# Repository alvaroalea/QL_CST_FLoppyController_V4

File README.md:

# QL_CST_FLoppyController

A clone of some version of the CST's Floppy Disk Interface for Sinclair QL

## History

CST was one of the main manufacturer of add-on for the Sinclair QL computer, this include backplanes, memory expansions and disc interfaces.

The Disk interface evolved over several version, with enhaced compatibilities in each version.

- Issue 1 - I can't get information about this Issue on internet.
- Issue 2 - This version use ReVision 1.13 (C) 1985 of the ROM, of 8Kb, Nicolaos Doukas draw the schematic an create a clone. Is possible to upgrade Issue 2 to ROM 1.16 if isolate the PIN 3 of IC3 (74LS03).
- Issue 3 - This version use Revision 1.16 (C) 198X of the ROM, of 8Kb, new clock circuit and 1 missing track on the PCB (and this is the reason you need to isolate pin 3 on Issue 2)
- Issue 4 - This version use Revision 1.18 (C) 1986 /1.19 (C) 1987 of the ROM, diferent circuit, increase the ROM size to 12Kb (use a 16Kb Eprom chip), now include RAM disk driver in rom, this version se a scrambled ROM, so when read with a external device, you can see the code.

Version 1.19 of ROM is missing in action, other version area available to download here: https://dilwyn.theqlforum.com/qlrom/index.html

Has been seen version of Issue 4 with, the top/botton cooper tracks interchanged, this help to reverse engineered the complete board.

Nowday I have draw and test the PCB of Issue 3 and 4, they are in separate folders, including, manuals and and ROM image.

## The Board

It use the standar stugart conector, so a plain cable can have up to 2 disk drives, that shall be correctly configured as DS0 and DS1.

It use a WD1770 disc controller, and is expected that will be compatible with WD1772 (not checked), WD1773 is not compatible.

Thanks to Derek_Stewart and techy of qlforum.co.uk for providing the pictures that allow me to capture the schema.

A interactive bill of materials for each board is available here:

* https://alvaroalea.github.io/QL_CST_FLoppyController/ibom_3.html
* https://alvaroalea.github.io/QL_CST_FLoppyController/ibom_4.html

### WARNING: Use good components!

During testing we found that bulk unknow 2N2222 transistor seen to work, but have hard compatibility problems with other boards.

Using a wellknow source transistor eliminate the incompatibility and work correctly with other passthrough boards. Be aware if you use a external or internal RAM expansion, a Qbide with passtrough or a backplane that allow several boarda.

## Recreated Boards

### Issue 4

### Issue 3

## Original Boards

### Issue 2

One of the few images available on internet, noted the transistor near the edge conector, 3 resistor on top of the PCB, two of this near the crystal, and the resistor array near WD1770 is called R4 (SIL)

### Issue 3

The transistor has been moved, the 3 resistor has been replaces by array R1, and the resistor array near WD1770 is called R2 (SIL)

### Issue 4

Complete new PCB, note The right one, with top/botton layer correct, but without silkscreen, and the left, with silkscreen but top/botton swapped (and exposed tracks under heat disipator).

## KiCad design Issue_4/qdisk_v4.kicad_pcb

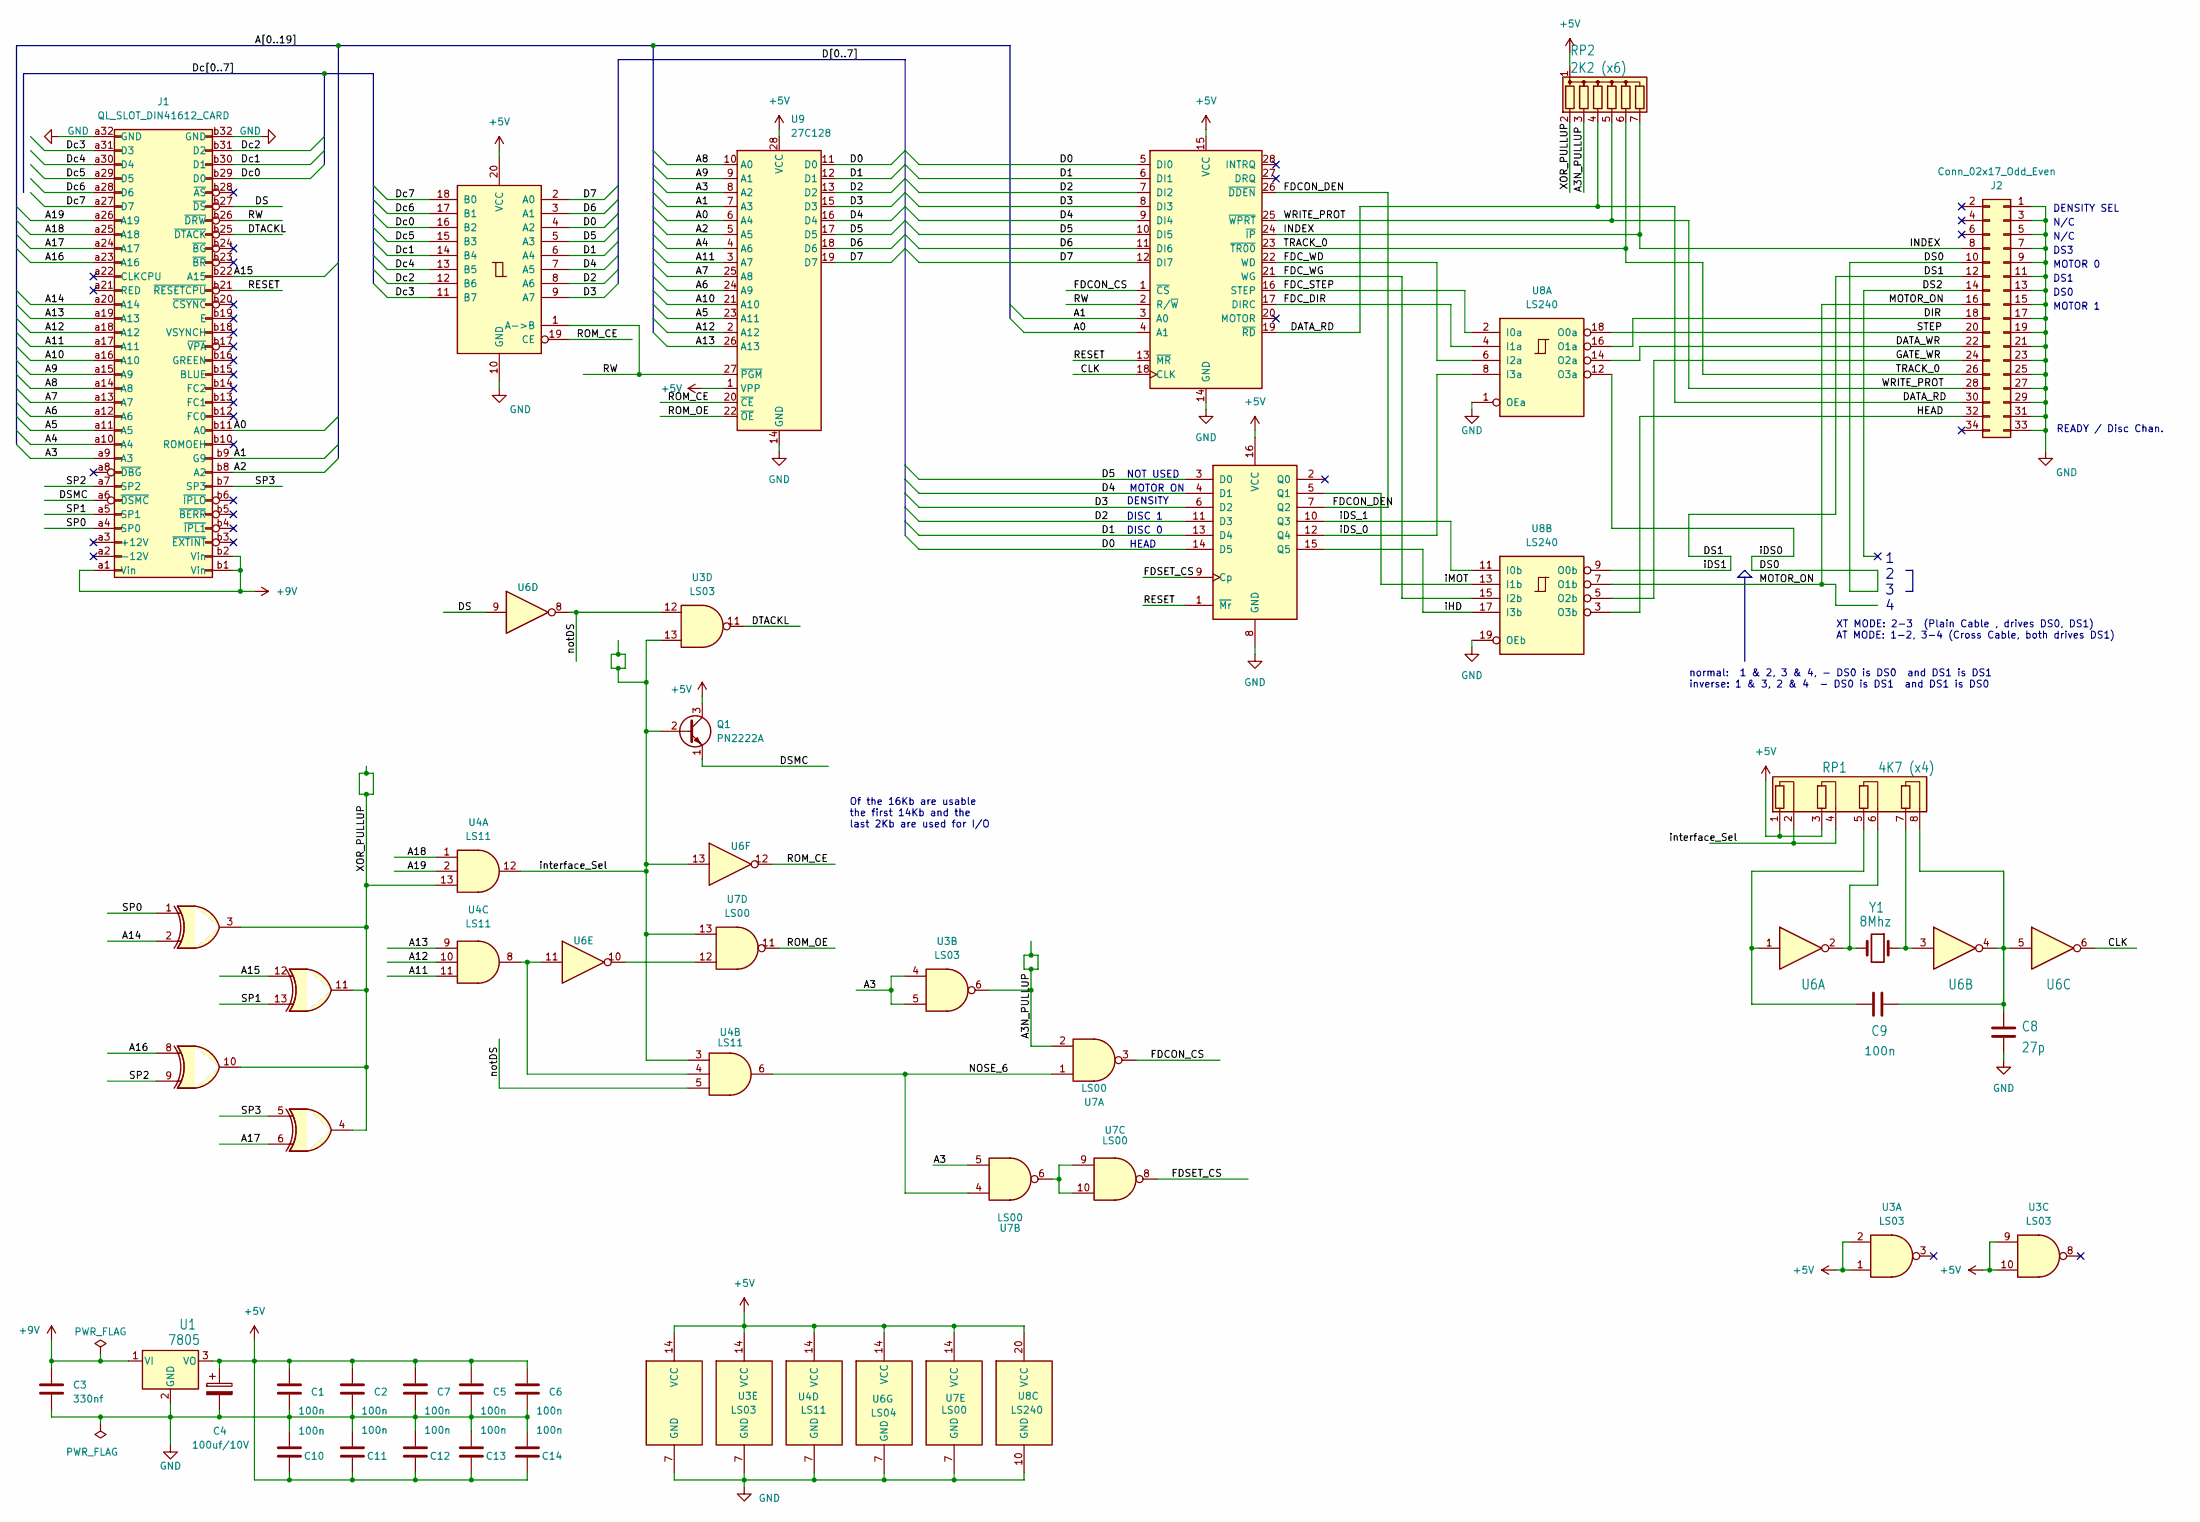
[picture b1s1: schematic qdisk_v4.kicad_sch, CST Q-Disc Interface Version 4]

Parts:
C1, C2, C5, C6, C7, C9, C10, C11, C12, C13, C14: 100n; C_Disc_D7.0mm_W2.5mm_P5.00mm
C3: 330nf; C_Disc_D7.0mm_W2.5mm_P5.00mm
C4: 100uf/10V; CP_Radial_D8.0mm_P5.00mm
C8: 27p; C_Disc_D7.0mm_W2.5mm_P5.00mm
J1: QL_SLOT_DIN41612_CARD; DIN41612_B_2x32_Female_Horizontal_THT
J2: Conn_02x17_Odd_Even; IDC-Header_2x17_P2.54mm_Latch_Horizontal
Q1: PN2222A; TO-92S_Wide
RP1: 4K7 (x4); R_Array_SIP8
RP2: 2K2 (x6); R_Array_SIP7
U1: 7805; TO-220-3_Horizontal_TabDown
U2: 74LS266; DIP-14_W7.62mm
U3: LS03; DIP-14_W7.62mm_Socket
U4: LS11; DIP-14_W7.62mm_Socket
U5: 74LS245; DIP-20_W7.62mm_Socket
U6: LS04; DIP-14_W7.62mm_Socket
U7: LS00; DIP-14_W7.62mm_Socket
U8: LS240; DIP-20_W7.62mm_Socket
U9: 27C128; DIP-28_W15.24mm_Socket
U10: FDC_WD1772; DIP-28_W15.24mm
U11: 74LS174; DIP-16_W7.62mm_Socket
Y1: 8Mhz; Crystal_HC18-U_Horizontal

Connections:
+5V: C1.1, C2.1, C4.1, C5.1, C6.1, C7.1, C10.1, C11.1, C12.1, C13.1, C14.1, Q1.3 (C), RP1.1 (R1.1), RP1.3 (R2.1), RP2.1 (common), U1.3 (VO), U2.14 (VCC), U3.1, U3.2, U3.9, U3.10, U3.14 (VCC), U4.14 (VCC), U5.20 (VCC), U6.14 (VCC), U7.14 (VCC), U8.20 (VCC), U9.1 (VPP), U9.28 (VCC), U10.15 (VCC), U11.16 (VCC)
+9V: C3.1, J1.a1 (Vin), J1.b1 (Vin), J1.b2 (Vin), U1.1 (VI)
/A0: J1.b11 (A0), U9.6 (A4), U10.4 (A1)
/A1: J1.b9 (G9), U9.7 (A3), U10.3 (A0)
/A2: J1.b8 (A2), U9.5 (A5)
/A3: J1.a9 (A3), U3.4, U3.5, U7.5, U9.8 (A2)
/A3N_PULLUP: RP2.3 (R2), U3.6, U7.2
/A4: J1.a10 (A4), U9.4 (A6)
/A5: J1.a11 (A5), U9.23 (A11)
/A6: J1.a12 (A6), U9.24 (A9)
/A7: J1.a13 (A7), U9.25 (A8)
/A8: J1.a14 (A8), U9.10 (A0)
/A9: J1.a15 (A9), U9.9 (A1)
/A10: J1.a16 (A10), U9.21 (A10)
/A11: J1.a17 (A11), U4.11, U9.3 (A7)
/A12: J1.a18 (A12), U4.10, U9.2 (A12)
/A13: J1.a19 (A13), U4.9, U9.26 (A13)
/A14: J1.a20 (A14), U2.2
/A15: J1.b22 (A15), U2.12
/A16: J1.a23 (A16), U2.8
/A17: J1.a24 (A17), U2.6
/A18: J1.a25 (A18), U4.1
/A19: J1.a26 (A19), U4.2
/CLK: U6.6, U10.18 (CLK)
/D0: U5.4 (A2), U9.11 (D0), U10.5 (DI0), U11.14 (D5)
/D1: U5.6 (A4), U9.12 (D1), U10.6 (DI1), U11.13 (D4)
/D2: U5.8 (A6), U9.13 (D2), U10.7 (DI2), U11.11 (D3)
/D3: U5.9 (A7), U9.15 (D3), U10.8 (DI3), U11.6 (D2)
/D4: U5.7 (A5), U9.16 (D4), U10.9 (DI4), U11.4 (D1)
/D5: U5.5 (A3), U9.17 (D5), U10.10 (DI5), U11.3 (D0)
/D6: U5.3 (A1), U9.18 (D6), U10.11 (DI6)
/D7: U5.2 (A0), U9.19 (D7), U10.12 (DI7)
/DATA_RD: J2.30, RP2.4 (R3), U10.19 (~RD)
/DATA_WR: J2.22, U8.14 (O2a)
/DIR: J2.18, U8.16 (O1a)
/DS: J1.b27 (~DS), U6.9
/DS0: J2.10, U8.12 (O3a)
/DS1: J2.12, U8.9 (O0b)
/DS2: J2.14
/DSMC: J1.a6 (~DSMC), Q1.1 (E)
/DTACKL: J1.b25 (~DTACK), U3.11
/Dc0: J1.b29 (D0), U5.16 (B2)
/Dc1: J1.b30 (D1), U5.14 (B4)
/Dc2: J1.b31 (D2), U5.12 (B6)
/Dc3: J1.a31 (D3), U5.11 (B7)
/Dc4: J1.a30 (D4), U5.13 (B5)
/Dc5: J1.a29 (D5), U5.15 (B3)
/Dc6: J1.a28 (D6), U5.17 (B1)
/Dc7: J1.a27 (D7), U5.18 (B0)
/FDCON_CS: U7.3, U10.1 (~CS)
/FDCON_DEN: U10.26 (~DDEN), U11.7 (Q2)
/FDC_DIR: U8.4 (I1a), U10.17 (DIRC)
/FDC_STEP: U8.2 (I0a), U10.16 (STEP)
/FDC_WD: U8.6 (I2a), U10.22 (WD)
/FDC_WG: U8.15 (I2b), U10.21 (WG)
/FDSET_CS: U7.8, U11.9 (Cp)
/GATE_WR: J2.24, U8.5 (O2b)
/HEAD: J2.32, U8.3 (O3b)
/INDEX: J2.8, RP2.7 (R6), U10.24 (~IP)
/MOTOR_ON: J2.16, U8.7 (O1b)
/NOSE_6: U4.6, U7.1, U7.4
/RESET: J1.b21 (~RESETCPU), U10.13 (~MR), U11.1 (~Mr)
/ROM_CE: U5.19 (CE), U6.12, U9.20 (~CE)
/ROM_OE: U7.11, U9.22 (~OE)
/RW: J1.b26 (~DRW), U5.1 (A->B), U9.27 (~PGM), U10.2 (R/~W)
/SP0: J1.a4 (SP0), U2.1
/SP1: J1.a5 (SP1), U2.13
/SP2: J1.a7 (SP2), U2.9
/SP3: J1.b7 (SP3), U2.5
/STEP: J2.20, U8.18 (O0a)
/TRACK_0: J2.26, RP2.6 (R5), U10.23 (~TR00)
/WRITE_PROT: J2.28, RP2.5 (R4), U10.25 (~WPRT)
/XOR_PULLUP: RP2.2 (R1), U2.3, U2.4, U2.10, U2.11, U4.13
/iDS_0: U8.8 (I3a), U11.12 (Q4)
/iDS_1: U8.11 (I0b), U11.10 (Q3)
/iHD: U8.17 (I3b), U11.15 (Q5)
/iMOT: U8.13 (I1b), U11.5 (Q1)
/interface_Sel: Q1.2 (B), RP1.2 (R1.2), RP1.4 (R2.2), U3.13, U4.3, U4.12, U6.13, U7.13
/notDS: U3.12, U4.5, U6.8
GND: C1.2, C2.2, C3.2, C4.2, C5.2, C6.2, C7.2, C8.2, C10.2, C11.2, C12.2, C13.2, C14.2, J1.a32 (GND), J1.b32 (GND), J2.1, J2.3, J2.5, J2.7, J2.9, J2.11, J2.13, J2.15, J2.17, J2.19, J2.21, J2.23, J2.25, J2.27, J2.29, J2.31, J2.33, U1.2 (GND), U2.7 (GND), U3.7 (GND), U4.7 (GND), U5.10 (GND), U6.7 (GND), U7.7 (GND), U8.1 (OEa), U8.10 (GND), U8.19 (OEb), U9.14 (GND), U10.14 (GND), U11.8 (GND)
unnamed: C9.2, RP1.5 (R3.1), U6.1
unnamed: RP1.6 (R3.2), U6.2, Y1.2
unnamed: RP1.7 (R4.1), U6.3, Y1.1
unnamed: C8.1, C9.1, RP1.8 (R4.2), U6.4, U6.5
unnamed: U4.4, U4.8, U6.11
unnamed: U6.10, U7.12
unnamed: U7.6, U7.9, U7.10

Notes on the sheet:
XT MODE: 2-3 (Plain Cable , drives DS0, DS1) AT MODE: 1-2, 3-4 (Cross Cable, both drives DS1)
NOT USED
MOTOR ON
MOTOR 0
HEAD
normal: 1 & 2, 3 & 4, - DS0 is DS0 and DS1 is DS1 inverse: 1 & 3, 2 & 4 - DS0 is DS1 and DS1 is DS0
DS0
DS1
READY / Disc Chan.
DENSITY
MOTOR 1
DS3
Of the 16Kb are usable the first 14Kb and the last 2Kb are used for I/O
N/C
1 2 3 4
DISC 1
DENSITY SEL
DISC 0

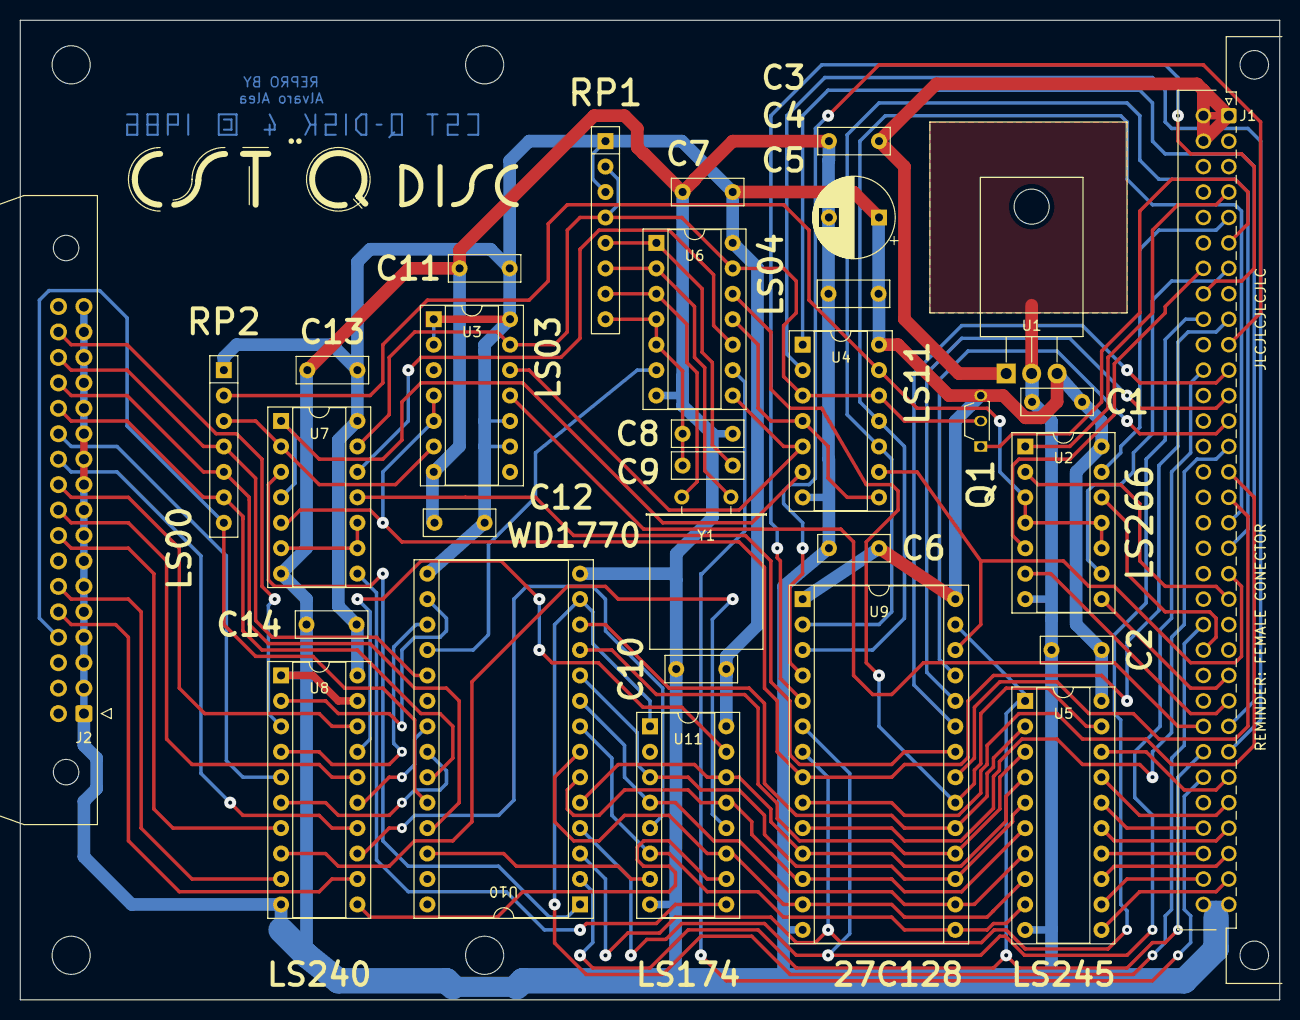
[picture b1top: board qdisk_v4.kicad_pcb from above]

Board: 2 copper layers, 125.7 x 97.8 mm, 31 parts (0 on the bottom side), 86 nets.

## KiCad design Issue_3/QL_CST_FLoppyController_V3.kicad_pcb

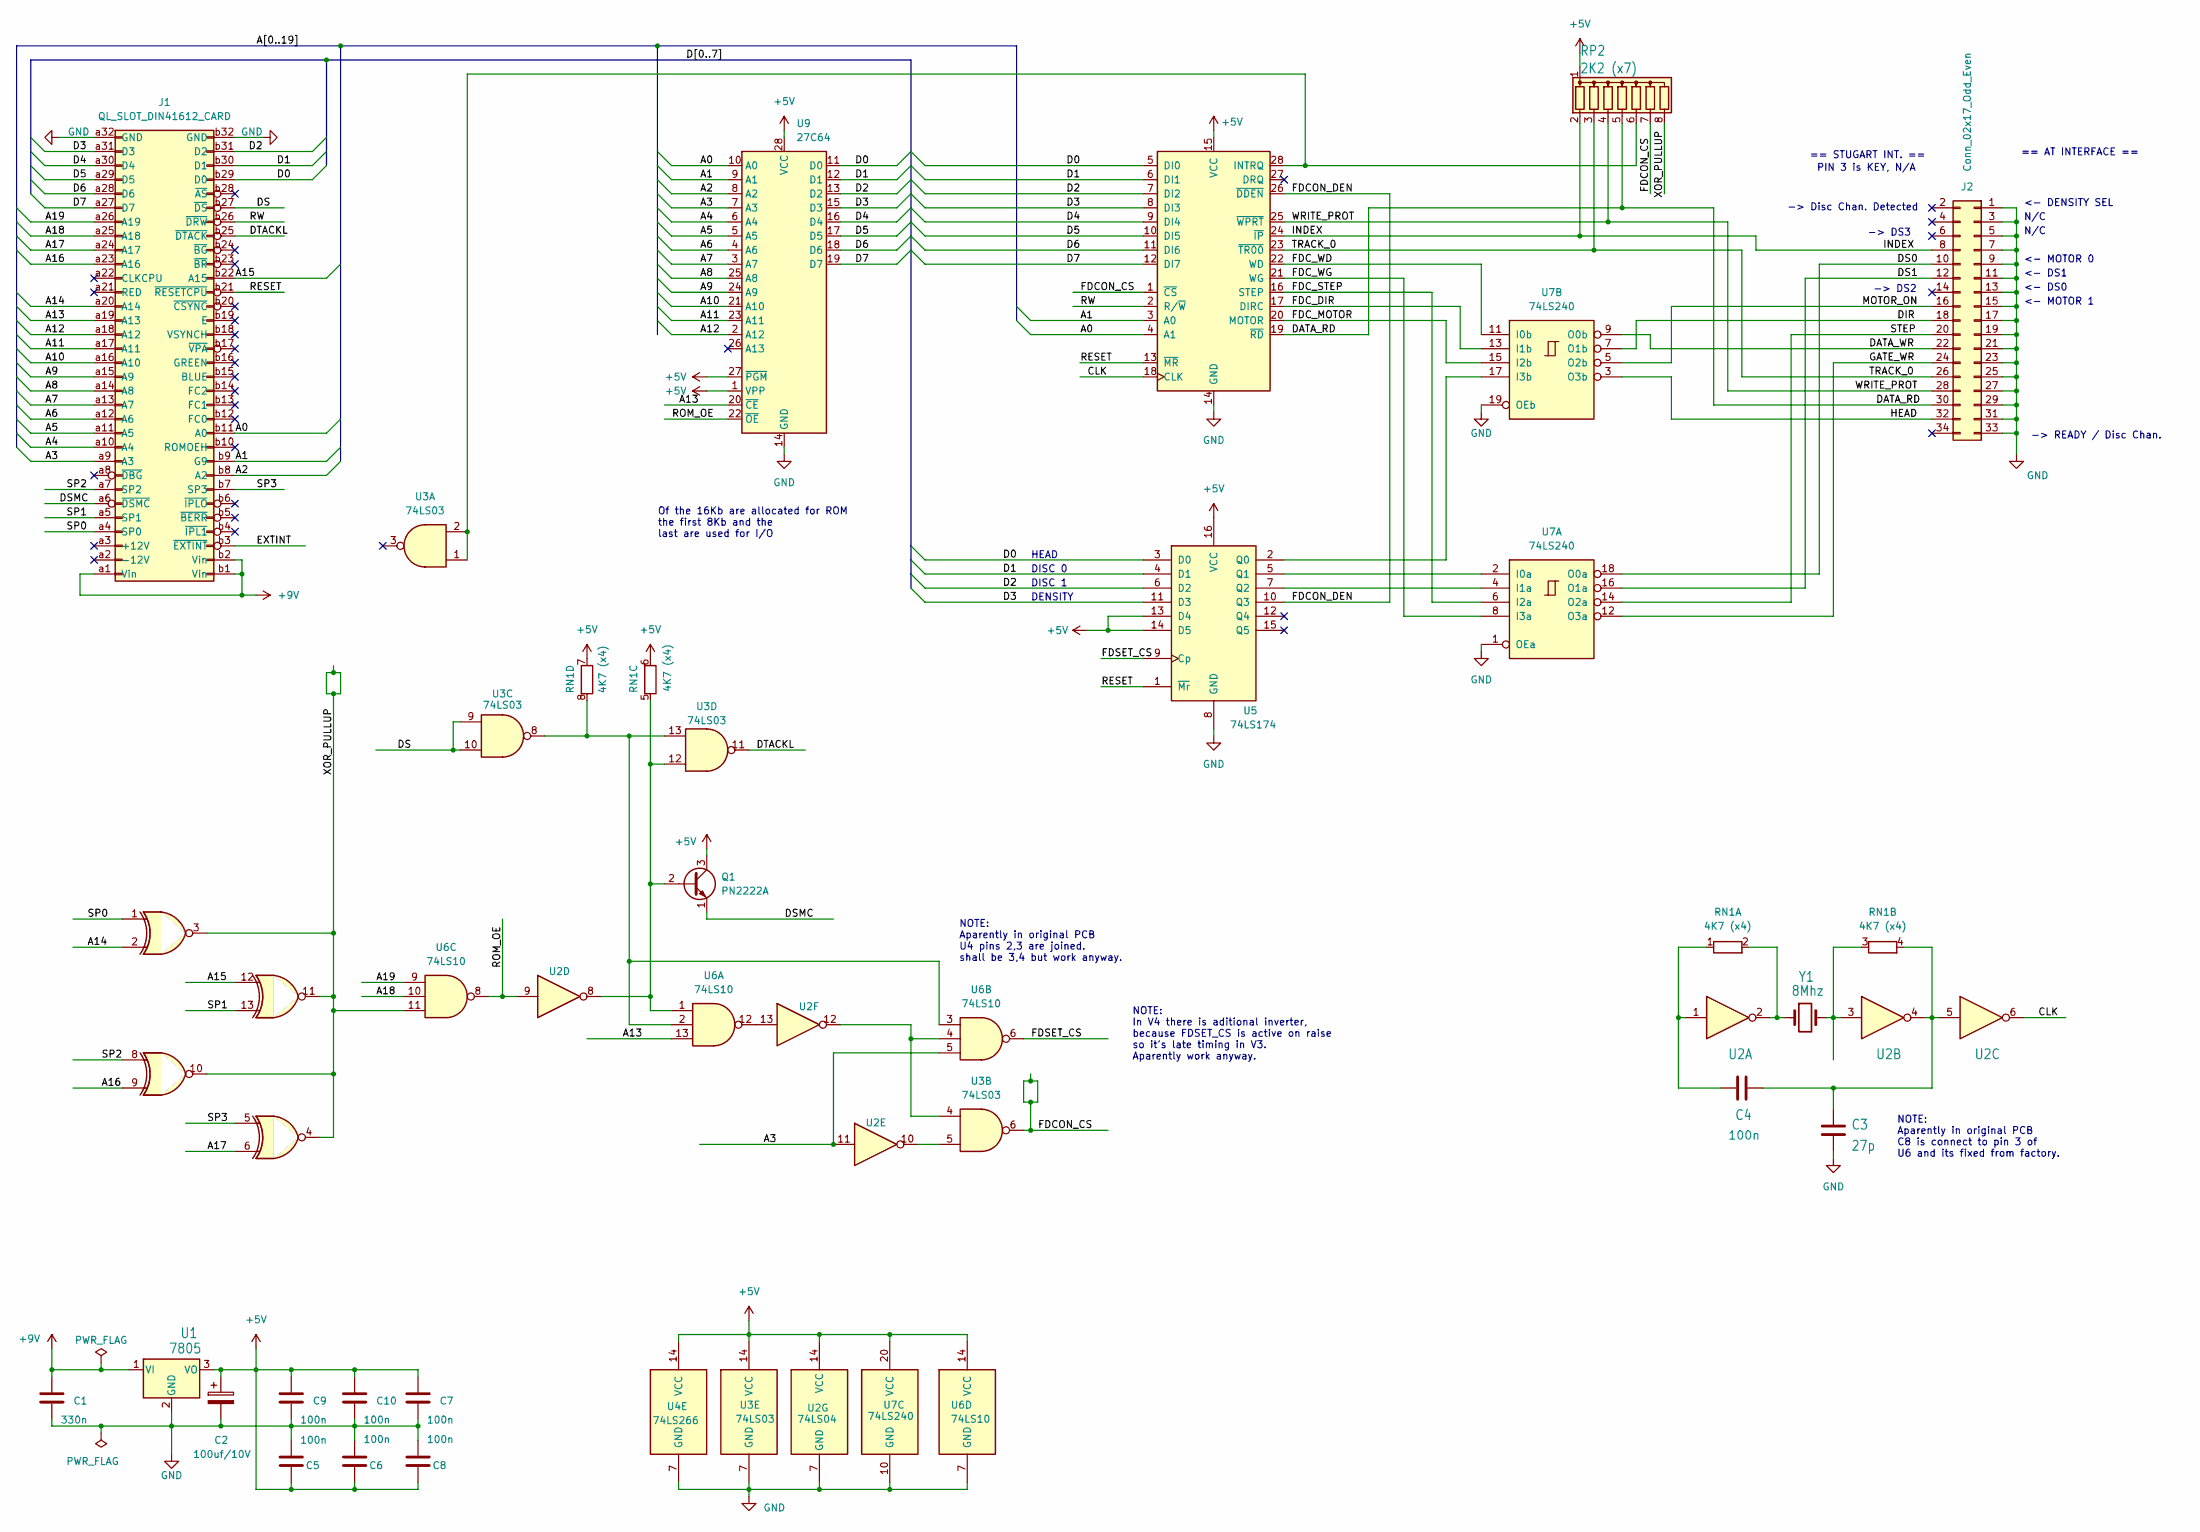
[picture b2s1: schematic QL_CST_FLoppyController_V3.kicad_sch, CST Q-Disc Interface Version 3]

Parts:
C1: 330n; C_Disc_D7.0mm_W2.5mm_P5.00mm
C2: 100uf/10V; CP_Radial_D8.0mm_P5.00mm
C3: 27p; C_Disc_D7.0mm_W2.5mm_P5.00mm
C4, C5, C6, C7, C8, C9, C10: 100n; C_Disc_D7.0mm_W2.5mm_P5.00mm
J1: QL_SLOT_DIN41612_CARD; DIN41612_B_2x32_Female_Horizontal_THT
J2: Conn_02x17_Odd_Even; IDC-Header_2x17_P2.54mm_Latch_Horizontal
Q1: PN2222A; TO-92_Wide
RN1: 4K7 (x4); R_Array_SIP8
RP2: 2K2 (x7); R_Array_SIP8
U1: 7805; TO-220-3_Horizontal_TabDown
U2: 74LS04; DIP-14_W7.62mm_Socket
U3: 74LS03; DIP-14_W7.62mm_Socket
U4: 74LS266; DIP-14_W7.62mm_Socket
U5: 74LS174; DIP-16_W7.62mm_Socket
U6: 74LS10; DIP-14_W7.62mm_Socket
U7: 74LS240; DIP-20_W7.62mm_Socket
U8: WD1772; DIP-28_W15.24mm_Socket
U9: 27C64; DIP-28_W15.24mm_Socket
Y1: 8Mhz; Crystal_HC18-U_Horizontal

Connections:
+5V: C2.1, C5.1, C6.1, C7.1, C8.1, C9.1, C10.1, Q1.3 (C), RN1.6 (R3.2), RN1.7 (R4.1), RP2.1 (common), U1.3 (VO), U2.14 (VCC), U3.14 (VCC), U4.14 (VCC), U5.13 (D4), U5.14 (D5), U5.16 (VCC), U6.14 (VCC), U7.20 (VCC), U8.15 (VCC), U9.1 (VPP), U9.27 (~PGM), U9.28 (VCC)
+9V: C1.1, J1.a1 (Vin), J1.b1 (Vin), J1.b2 (Vin), U1.1 (VI)
/A0: J1.b11 (A0), U8.4 (A1), U9.10 (A0)
/A1: J1.b9 (G9), U8.3 (A0), U9.9 (A1)
/A2: J1.b8 (A2), U9.8 (A2)
/A3: J1.a9 (A3), U2.11, U6.5, U9.7 (A3)
/A4: J1.a10 (A4), U9.6 (A4)
/A5: J1.a11 (A5), U9.5 (A5)
/A6: J1.a12 (A6), U9.4 (A6)
/A7: J1.a13 (A7), U9.3 (A7)
/A8: J1.a14 (A8), U9.25 (A8)
/A9: J1.a15 (A9), U9.24 (A9)
/A10: J1.a16 (A10), U9.21 (A10)
/A11: J1.a17 (A11), U9.23 (A11)
/A12: J1.a18 (A12), U9.2 (A12)
/A13: J1.a19 (A13), U6.13, U9.20 (~CE)
/A14: J1.a20 (A14), U4.2
/A15: J1.b22 (A15), U4.12
/A16: J1.a23 (A16), U4.9
/A17: J1.a24 (A17), U4.6
/A18: J1.a25 (A18), U6.10
/A19: J1.a26 (A19), U6.9
/CLK: U2.6, U8.18 (CLK)
/D0: J1.b29 (D0), U5.3 (D0), U8.5 (DI0), U9.11 (D0)
/D1: J1.b30 (D1), U5.4 (D1), U8.6 (DI1), U9.12 (D1)
/D2: J1.b31 (D2), U5.6 (D2), U8.7 (DI2), U9.13 (D2)
/D3: J1.a31 (D3), U5.11 (D3), U8.8 (DI3), U9.15 (D3)
/D4: J1.a30 (D4), U8.9 (DI4), U9.16 (D4)
/D5: J1.a29 (D5), U8.10 (DI5), U9.17 (D5)
/D6: J1.a28 (D6), U8.11 (DI6), U9.18 (D6)
/D7: J1.a27 (D7), U8.12 (DI7), U9.19 (D7)
/DATA_RD: J2.30, RP2.5 (R4), U8.19 (~RD)
/DATA_WR: J2.22, U7.9 (O0b)
/DIR: J2.18, U7.7 (O1b)
/DS: J1.b27 (~DS), U3.9, U3.10
/DS0: J2.10, U7.18 (O0a)
/DS1: J2.12, U7.16 (O1a)
/DSMC: J1.a6 (~DSMC), Q1.1 (E)
/DTACKL: J1.b25 (~DTACK), U3.11
/EXTINT: J1.b3 (~EXTINT)
/FDCON_CS: RP2.7 (R6), U3.6, U8.1 (~CS)
/FDCON_DEN: U5.10 (Q3), U8.26 (~DDEN)
/FDC_DIR: U7.13 (I1b), U8.17 (DIRC)
/FDC_MOTOR: U7.15 (I2b), U8.20 (MOTOR)
/FDC_STEP: U7.6 (I2a), U8.16 (STEP)
/FDC_WD: U7.11 (I0b), U8.22 (WD)
/FDC_WG: U7.8 (I3a), U8.21 (WG)
/FDSET_CS: U5.9 (Cp), U6.6
/GATE_WR: J2.24, U7.12 (O3a)
/HEAD: J2.32, U7.3 (O3b)
/INDEX: J2.8, RP2.2 (R1), U8.24 (~IP)
/MOTOR_ON: J2.16, U7.5 (O2b)
/RESET: J1.b21 (~RESETCPU), U5.1 (~Mr), U8.13 (~MR)
/ROM_OE: U2.9, U6.8, U9.22 (~OE)
/RW: J1.b26 (~DRW), U8.2 (R/~W)
/SP0: J1.a4 (SP0), U4.1
/SP1: J1.a5 (SP1), U4.13
/SP2: J1.a7 (SP2), U4.8
/SP3: J1.b7 (SP3), U4.5
/STEP: J2.20, U7.14 (O2a)
/TRACK_0: J2.26, RP2.3 (R2), U8.23 (~TR00)
/WRITE_PROT: J2.28, RP2.4 (R3), U8.25 (~WPRT)
/XOR_PULLUP: RP2.8 (R7), U4.3, U4.4, U4.10, U4.11, U6.11
GND: C1.2, C2.2, C3.2, C5.2, C6.2, C7.2, C8.2, C9.2, C10.2, J1.a32 (GND), J1.b32 (GND), J2.1, J2.3, J2.5, J2.7, J2.9, J2.11, J2.13, J2.15, J2.17, J2.19, J2.21, J2.23, J2.25, J2.27, J2.29, J2.31, J2.33, U1.2 (GND), U2.7 (GND), U3.7 (GND), U4.7 (GND), U5.8 (GND), U6.7 (GND), U7.1 (OEa), U7.10 (GND), U7.19 (OEb), U8.14 (GND), U9.14 (GND)
unnamed: Q1.2 (B), RN1.5 (R3.1), U2.8, U3.12, U6.1
unnamed: C4.2, RN1.1 (R1.1), U2.1
unnamed: RN1.2 (R1.2), U2.2, Y1.1
unnamed: RN1.3 (R2.1), U2.3, Y1.2
unnamed: C3.1, C4.1, RN1.4 (R2.2), U2.4, U2.5
unnamed: RN1.8 (R4.2), U3.8, U3.13, U6.2, U6.3
unnamed: RP2.6 (R5), U3.1, U3.2, U8.28 (INTRQ)
unnamed: U2.10, U3.5
unnamed: U2.12, U3.4, U6.4
unnamed: U2.13, U6.12
unnamed: U5.2 (Q0), U7.17 (I3b)
unnamed: U5.5 (Q1), U7.2 (I0a)
unnamed: U5.7 (Q2), U7.4 (I1a)

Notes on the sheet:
== STUGART INT. ==
NOTE: In V4 there is aditional inverter, because FDSET_CS is active on raise so it's late timing in V3. Aparently work anyway.
PIN 3 is KEY, N/A
<- MOTOR 0
HEAD
-> DS3
NOTE: Aparently in original PCB U4 pins 2,3 are joined. shall be 3,4 but work anyway.
<- DS0
<- DS1
-> READY / Disc Chan.
DENSITY
-> Disc Chan. Detected
<- MOTOR 1
NOTE: Aparently in original PCB C8 is connect to pin 3 of U6 and its fixed from factory.
Of the 16Kb are allocated for ROM the first 8Kb and the last are used for I/O
N/C
-> DS2
DISC 1
== AT INTERFACE ==
<- DENSITY SEL
DISC 0

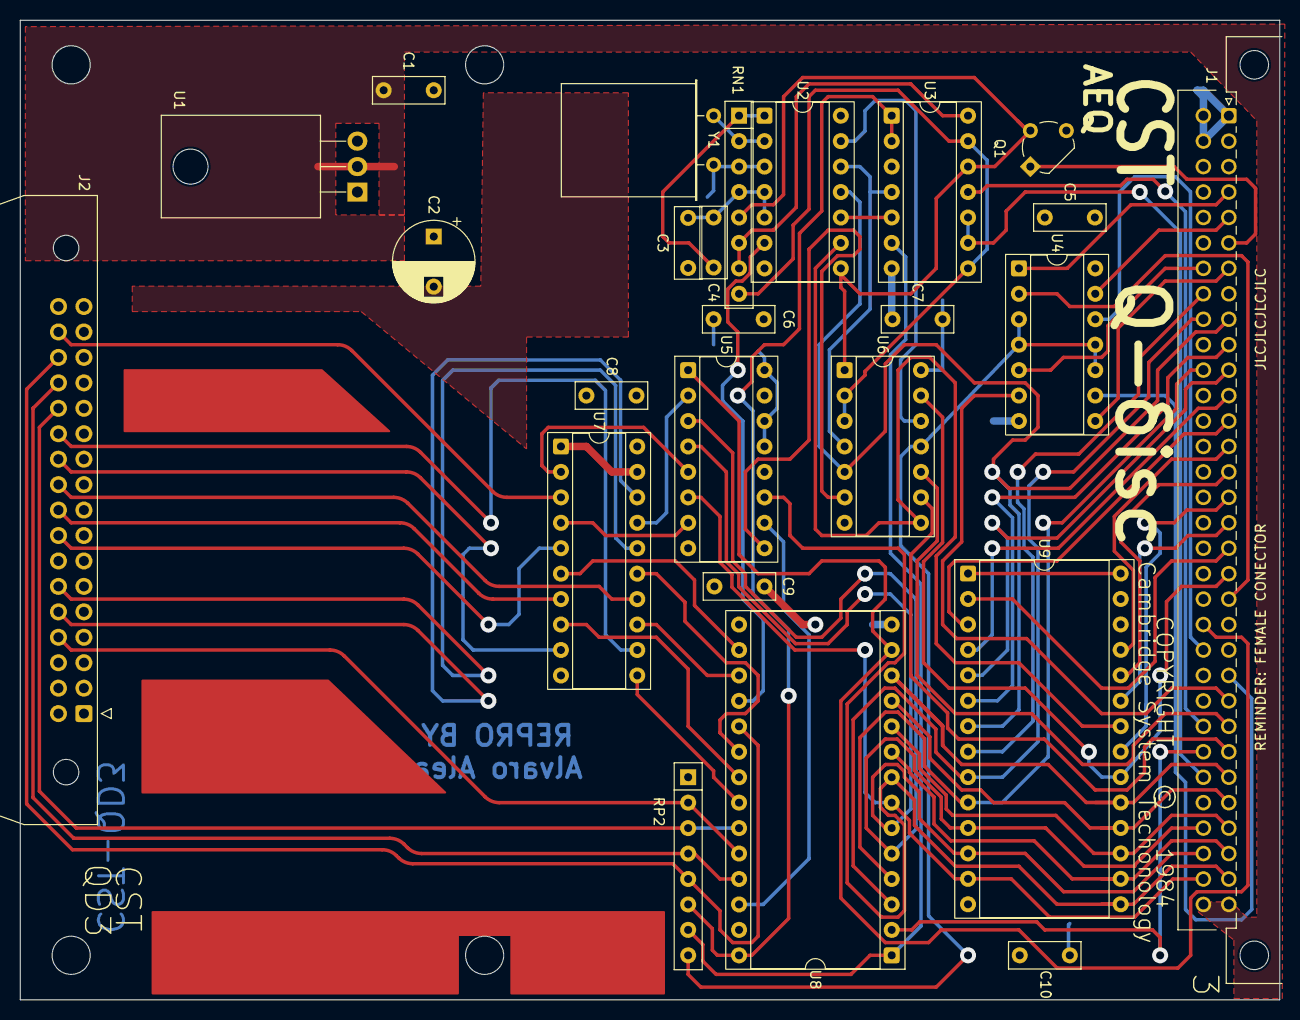
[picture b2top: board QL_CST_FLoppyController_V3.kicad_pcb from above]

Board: 2 copper layers, 125.7 x 97.8 mm, 25 parts (0 on the bottom side), 76 nets.

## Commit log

2023-05-20 Finish Schematic capture. Upgraded to Kicad 7. Ordered testing PCB
2023-05-20 Remove background images so PCB 50MB -> 500kB
2023-06-16 Add manual, 3d case and small corrections
2023-06-17 Small corrections in the 3D model of the case
2025-04-27 initial Issue 3

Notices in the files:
Issue_3/QL_CST_FLoppyController_V3.kicad_pcb:
COPYRIGHT © 1984
Licensed under Cern OHL-S
